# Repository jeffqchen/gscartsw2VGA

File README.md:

# gscartsw2VGA
A VGA adapter for the gscartsw

This adapter converts the SCART ports on the gscartsw into D-Sub HD15 ports that accepts RGBS video signal as well as stereo audio. This is a link among my [series of VGA dongles](https://github.com/jeffqchen/Console-VGA-Dongle-Series) to deal with various consoles and video switches using the RGBS video signal.

The adapter consists of, as simple as, a D-Sub HD15 port, a piece of PCB, a SCART male plug, and 3D printed shells.

-----

## Parts

- [PCB](https://oshpark.com/shared_projects/UT8RVECU)

- VGA Port Slim Female - [Link](https://github.com/jeffqchen/JeffParts/blob/main/Connectors/HD15/Slim/Female%20PCB/info.md)

- SCART Male Plug, Cable Type - [Link](https://github.com/jeffqchen/JeffParts/blob/main/Connectors/SCART/Male%20Cable/info.md)

- [2x]M3x16mm, [1x]M3x8mm Hex Screws and Nuts - [Link](https://github.com/jeffqchen/JeffParts/blob/main/Parts/M2%20M3%20Hex%20Screw%20%26%20Nut/info.md)

3D Printed Shell

------

## 3D Printing

Print the parts in their orientation in the STL file with supports.

Choose the corresponding big side of the shell for input or output.

------

## Assembly

Clean up all the edges of the PCB, as there is no extra space inside the shell for any imperfection on the PCB.

Bridge the 3 jumpers on the PCB according to your use case. The star side of the jumpers mean INPUT. The other side is used for OUTPUT.

Solder in the VGA port on the side with the silk print "VGA".

Fit on the 3D printed VGA face panel, then slide the assembly into the big side of the shell, then fit in the SCART male plug.

Solder in at least two pins on the SCART plug to hold it in place. Then, take the assembly out of the 3D printed shell, and then proceed to solder the rest of the SCART plug pins onto the PCB with ample amount of solder.

Finally, put the VGA face panel back onto the internal assembly, and fit the assembly into the big side of the shell. Then close it up with the small side of th shell with the 3 sets of screws and nuts.

------

## Fitment Onto the gscartsw

Hook the curvy end of the adapter onto the edge of the acrylic panel. Align the SCART plug with one of the female SCART port on the switch. Then slightly pry the flap on the other end outwards with your index finger, so the hook on that side can safely pass the acrylic panel. Press the adapter flat and then let go.

------
Shield: [![CC BY-SA 4.0][cc-by-sa-shield]][cc-by-sa]

This work is licensed under a
[Creative Commons Attribution-ShareAlike 4.0 International License][cc-by-sa].

[![CC BY-SA 4.0][cc-by-sa-image]][cc-by-sa]

[cc-by-sa]: http://creativecommons.org/licenses/by-sa/4.0/
[cc-by-sa-image]: https://licensebuttons.net/l/by-sa/4.0/88x31.png
[cc-by-sa-shield]: https://img.shields.io/badge/License-CC%20BY--SA%204.0-lightgrey.svg

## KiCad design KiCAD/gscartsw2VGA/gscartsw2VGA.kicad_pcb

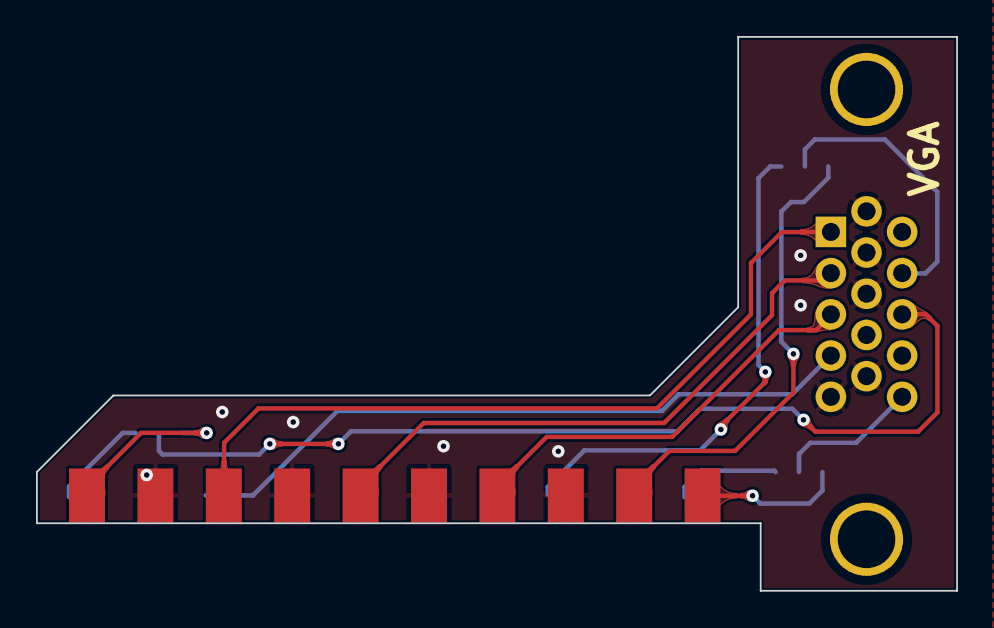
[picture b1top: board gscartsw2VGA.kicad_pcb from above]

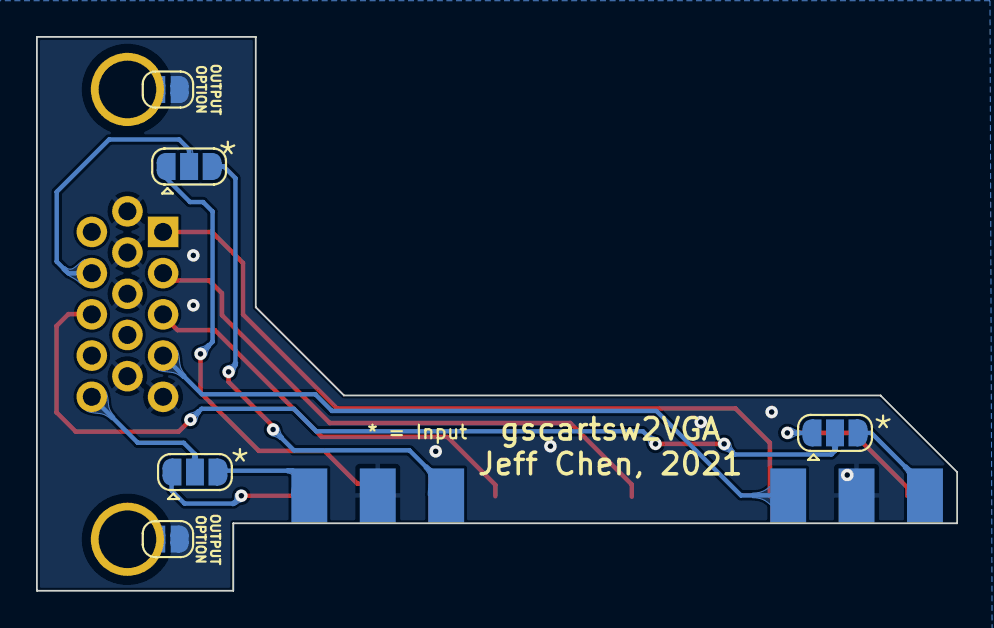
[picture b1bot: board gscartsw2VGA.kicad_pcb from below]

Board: 2 copper layers, 51.1 x 30.8 mm, 7 parts (5 on the bottom side), 16 nets.

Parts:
JP1, JP2, JP3: SolderJumper_3_Open; SolderJumper-3_P1.3mm_Open_RoundedPad1.0x1.5mm
JP4, JP5: Shield Ground; SolderJumper-2_P1.3mm_Open_RoundedPad1.0x1.5mm
P1: VGA; VGA_female_rightangle_slim
P2: SCART_PAL; SCART_Cutdown

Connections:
/Audio_L_In: JP2.3 (B), P2.6 (Audio_L_In)
/Audio_L_Out: JP2.1 (A), P2.3 (Audio_L_Out)
/Audio_L_VGA: JP2.2 (C), P1.12 (ID1/SDA)
/Audio_R_In: JP3.3 (B), P2.2 (Audio_R_In)
/Audio_R_Out: JP3.1 (A), P2.1 (Audio_R_Out)
/Audio_R_VGA: JP3.2 (C), P1.15 (ID3/SCL)
/Blue: P1.3 (Blue), P2.7 (Blue)
/CVBS_In: JP1.3 (B), P2.20 (CVBS_In)
/CVBS_Out: JP1.1 (A), P2.19 (CVBS_Out)
/Green: P1.2 (Green), P2.11 (Green)
/Red: P1.1 (Red), P2.15 (Red)
/Sync: JP1.2 (C), P1.13 (HSYNC)
GND: JP4.2 (B), JP5.2 (B), P1.5 (HSYNC_GND), P1.6 (Red_GND), P1.7 (Green_GND), P1.8 (Blue_GND), P1.10 (VSYNC_GND), P2.4 (Audio_GND), P2.5 (Blue_GND), P2.9 (Green_GND), P2.13 (Red_GND), P2.17 (CVBS_Out_GND), P2.18 (CVBS_In_GND)
unnamed: JP4.1 (A), P1.S1 (SHIELD)
unnamed: JP5.1 (A), P1.S2 (SHIELD)
unnamed: P1.4 (ID2/RES), P2.16 (Fast_switching)

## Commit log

2021-10-14 Initial Upload
2021-10-14 3D Print Files
2021-10-24 Change PCB
2022-08-09 Change license type
2022-10-18 Add shielding grounding option
2025-08-15 Multiple Adjustments
    - Add cable shielding grounding options
    - Adjust 3D print details to allow for easier printing and assembly
